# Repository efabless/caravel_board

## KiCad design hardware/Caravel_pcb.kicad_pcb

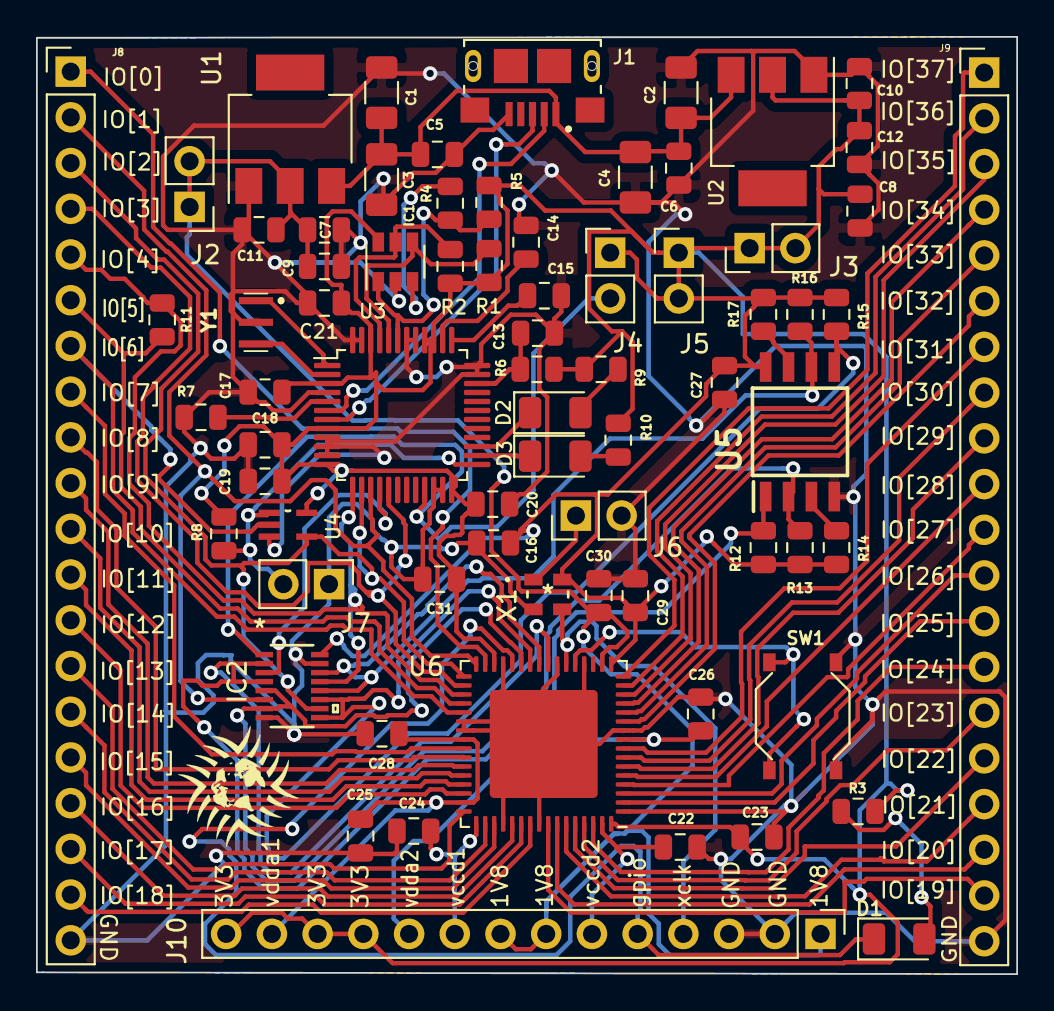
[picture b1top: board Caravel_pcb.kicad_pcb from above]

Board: 2 copper layers, 54.5 x 52.1 mm, 73 parts (0 on the bottom side), 76 nets.

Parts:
C1, C2, C3, C4: 100uf - GRM31CR60J107ME39L; C_1206_3216Metric
C5, C6, C9, C10: 10uf - CC0805KKX5R8BB106; C_0805_2012Metric
C7, C8: 22uf - CC0805MKX5R5BB226; C_0805_2012Metric
C11, C12: 1uf; C_0805_2012Metric
C13: 0.01uf - CC0805JRX7R9BB103; C_0805_2012Metric
C14, C15, C16, C17, C18, C19, C20, C21, C22, C23, C24, C25, C26, C27, C28, C29, C30, C31: 0.1uf - CC0805KRX7R9BB104; C_0805_2012Metric
D1, D2, D3: LED - 17-215SURC/S530-A2/TR8; LED_1206_3216Metric
IC1: 93C56; SOT-23-6
IC2: TMUX1574DYYR
J1: USB_B_Micro - 10118193-0001LF; FCI_10118193-0001LF
J2, J3, J4, J5, J6: Conn_01x02_Male; PinHeader_1x02_P2.54mm_Vertical
J7: Conn_01x02_Female; PinHeader_1x02_P2.54mm_Vertical
J8, J9: Conn_01x20_Female; PinHeader_1x20_P2.54mm_Vertical
J10: Conn_01x14_Female; PinHeader_1x14_P2.54mm_Vertical
R1, R2, R5, R6, R12, R13, R14, R15, R16, R17: 10k - RC0805FR-0710KL; R_0805_2012Metric
R3: 82 - 0805W8F820JT5E; R_0805_2012Metric
R4: 2K - CR0805J80202G; R_0805_2012Metric
R7: 12K 1% - 0805W8F1202T5E; R_0805_2012Metric
R8: 10k; R_0805_2012Metric
R9, R10: 150 - 0805W8J0151T5E; R_0805_2012Metric
R11: 0; R_0805_2012Metric
SW1: SW_Push - SKQGADE010; SW4-SMD-5.2X5.2X1.5MM
T1: Logo; logo
U1: AZ1117CH-1.8TRG1; SOT-223
U2: AZ1117-3.3; SOT-223
U3: FT232H; LQFP-48_7x7mm_P0.5mm
U4: SN74LVC1G125DCKR; SOT65P210X110-5N
U5: W25Q32FVSS; SOIC127P790X216-8N
U6: Caravel; QFN-64-1EP_9x9mm_P0.5mm_EP6x6mm
X1: DSC6001_10MHZ; DSC6001JE1A-010.0000
Y1: CSTNE12M0GH5L000R0

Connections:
+1V8: C7.2, C9.2, C11.2, C30.2, J2.1, J2.2, J10.1, J10.7, J10.8, U1.2, U6.18
+5V: C1.2, C2.2, C3.2, C4.2, C5.2, C6.2, J1.1, U1.3, U2.3
Caravel_CSB: IC2.2, IC2.4, R12.1, U5.1, U6.24
Caravel_D0: IC2.9, IC2.11, R15.1, U5.5, U6.26
Caravel_D1: IC2.5, IC2.7, R13.1, U5.2, U6.27
Caravel_SCK: IC2.12, IC2.14, R16.1, U5.6, U6.25
EECLK: IC1.4, R1.1, U3.44
EECS: IC1.5, R2.1, U3.45
EEDATA: IC1.1, R4.2, R5.2, U3.43
FTDI_D+: J1.3, U3.7
FTDI_D-: J1.2, U3.6
GND: C1.1, C2.1, C3.1, C4.1, C5.1, C6.1, C7.1, C8.1, C9.1, C10.1, C11.1, C12.1, C13.1, C14.1, C15.1, C16.1, C17.1, C18.1, C19.1, C20.1, C21.1, C22.1, C23.1, C24.2, C25.1, C26.1, C27.2, C28.2, C29.1, C30.1, C31.2, IC1.2, IC2.8, IC2.15, J1.5, J6.2, J7.1, J8.20, J9.20, J10.2, J10.3, R7.1, SW1.2, U1.1, U2.1, U3.4, U3.9, U3.10, U3.11, U3.22, U3.23, U3.35, U3.36, U3.41, U3.42, U3.47, U3.48, U4.3, U5.4, U6.1, U6.10, U6.20, U6.23, U6.29, U6.38, U6.39, U6.52, U6.56, U6.65, X1.2, Y1.2
unnamed: C13.2, R6.1, U3.34
unnamed: C14.2, U3.38
unnamed: C15.2, U3.37
unnamed: D1.2, R3.2
unnamed: D2.1, U3.27
unnamed: D2.2, R9.1
unnamed: D3.1, U3.26
unnamed: D3.2, R10.1
unnamed: IC1.3, R4.1
unnamed: J6.1, X1.1
unnamed: R7.2, U3.5
unnamed: R14.1, U5.3
unnamed: R17.1, U5.7
unnamed: U3.1, Y1.1
unnamed: U3.2, Y1.3
TMUX_SEL: IC2.1, J4.2, U3.21
TXD_EN: J7.2, R8.2, U3.25, U4.1
USB_CS1: IC2.3, U3.16
USB_CS2: J8.4, U3.17, U6.34
USB_SCK_TXD: IC2.13, J8.5, R11.2, U3.13, U6.35
USB_SI: IC2.6, J8.2, U3.15, U6.32
USB_SO_RXD: IC2.10, J8.3, U3.14, U4.4, U6.33
gpio: D1.1, J10.5, U6.28
mprj_io[0]: J8.1, U6.31
mprj_io[5]_ser_rx: J8.6, R11.1, U6.36
mprj_io[6]_ser_tx: J8.7, U4.2, U6.37
mprj_io[7]: J8.8, U6.41
mprj_io[8]: J8.9, U6.42
mprj_io[9]: J8.10, U6.43
mprj_io[10]: J8.11, U6.44
mprj_io[11]: J8.12, U6.45
mprj_io[12]: J8.13, U6.46
mprj_io[13]: J8.14, U6.48
mprj_io[14]: J8.15, U6.50
mprj_io[15]: J8.16, U6.51
mprj_io[16]: J8.17, U6.53
mprj_io[17]: J8.18, U6.54
mprj_io[18]: J8.19, U6.55
mprj_io[19]: J9.19, U6.57
mprj_io[20]: J9.18, U6.58
mprj_io[21]: J9.17, U6.59
mprj_io[22]: J9.16, U6.60
mprj_io[23]: J9.15, U6.61
mprj_io[24]: J9.14, U6.62
mprj_io[25]: J9.13, U6.2
mprj_io[26]: J9.12, U6.3
mprj_io[27]: J9.11, U6.4
mprj_io[28]: J9.10, U6.5
mprj_io[29]: J9.9, U6.6
mprj_io[30]: J9.8, U6.7
mprj_io[31]: J9.7, U6.8
mprj_io[32]: J9.6, U6.11
mprj_io[33]: J9.5, U6.12
mprj_io[34]: J9.4, U6.13
mprj_io[35]: J9.3, U6.14
mprj_io[36]: J9.2, U6.15
mprj_io[37]: J9.1, U6.16
vccd1: C24.1, J10.9, U6.49
vccd2: C22.2, J10.6, U6.63
vdda1: C25.2, C28.1, J10.13, U6.40, U6.47
vdda2: C26.2, J10.10, U6.9
vddio: C8.2, C10.2, C12.2, C16.2, C17.2, C18.2, C19.2, C20.2, C21.2, C23.2, C27.1, C29.2, C31.1, IC1.6, IC2.16, J3.1, J3.2, J4.1, J5.1, J5.2, J10.11, J10.12, J10.14, R1.2, R2.2, R3.1, R5.1, R6.2, R8.1, R9.2, R10.2, R12.2, R13.2, R14.2, R15.2, R16.2, R17.2, U2.2, U3.3, U3.8, U3.12, U3.24, U3.39, U3.40, U3.46, U4.5, U5.8, U6.17, U6.30, U6.64, X1.4
xclk: J10.4, U6.22, X1.3
~RST: SW1.1, U6.21

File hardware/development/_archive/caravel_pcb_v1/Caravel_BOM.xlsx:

Designators | QTY | Value | Part Number | Supplier
U6 | 1 |  | Caravel | EF
U5 | 1 |  | W25Q32JVSSIQ | DK
U4 | 1 |  | SN74LVC1G125DCKT | Mouser | alternative part
U3 | 1 |  | FT232H | not stocked
U2 | 1 |  | NCP1117LPST33T3G | DK | alternative part
U1 | 1 |  | AZ1117CH-1.8TRG1 | DK
IC1 | 0 |  | 93C56 | don't install
IC2 | 0 |  | TMUX1574DYYR | not stocked
D1, D2, D3 | 3 |  | LTST-C230KRKT | DK
C1, C2, C3, C4 | 4 | 100u | GMC31X5R107M6R3NT | DK | GMC31X5R107M6R3NT
C5, C6, C9, C10 | 4 | 10u | CC0805KKX5R8BB106 | DK
C7, C8 | 2 | 22u | CC0805MKX5R5BB226 | DK
C11, C12 | 2 | 1u | CC0805KKX7R8BB105 | DK
C14-C31 | 18 | 0.1u | CC0805KRX7R9BB104 | DK
C13 | 1 | 0.01u | CC0805JRX7R9BB103 | DK
R1, R2, R5, R6, R8, R12-R17 | 11 | 10K | RC0805FR-0710KL | DK
R7 | 1 | 12K, 1% | RMCF0805FT12K0 | DK
R9, R10 | 2 | 150 | RNCP0805FTD150R | DK
R3 | 1 | 82 | RMCF0805FT82R0 | DK
R4 | 1 | 2K | RMCF0805FT2K00 | DK
R11 | 1 | 0 | RK73Z2ATTD | DK
J1 | 1 |  | 10118193-0001LF | DK
X1 | 1 | 10MHz | DSC6001JE1A-010.0000 | DK
Y1 | 1 | 12MHz | CSTNE12M0GH5L000R0 | Mouser

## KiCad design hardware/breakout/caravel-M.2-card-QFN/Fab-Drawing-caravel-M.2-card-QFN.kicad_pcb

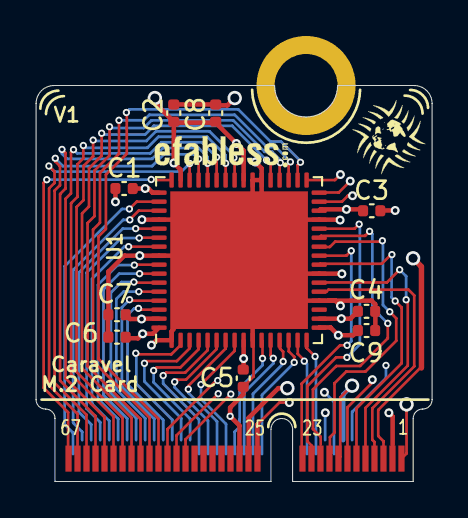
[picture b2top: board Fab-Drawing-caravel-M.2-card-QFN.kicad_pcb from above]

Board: 4 copper layers, 22.0 x 22.0 mm, 13 parts (0 on the bottom side), 53 nets.

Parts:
C1, C2, C3, C4, C5, C6, C7, C8, C9: 0.1uf; C_0402_1005Metric
J1: MICROMOD-2222-Generic; MicroMod-M.2-CARD-E-22
T1: Logo; logo_small
T2: Logo; ef_logo
U1: Caravel; QFN-64-1EP_9x9mm_P0.5mm_EP7.65x7.65mm

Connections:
Caravel_CSB: J1.11, U1.24 (flash_csb)
Caravel_D0: J1.17, U1.26 (flash_io0)
Caravel_D1: J1.19, U1.27 (flash_io1)
Caravel_SCK: J1.23, U1.25 (flash_clk)
GND: C1.1, C2.2, C3.2, C4.1, C5.1, C6.1, C7.1, C8.2, C9.1, J1.12, J1.18, J1.37 (P29), J1.GND, U1.1 (vssa2), U1.10 (vssd2), U1.20 (vssa), U1.23 (vssd), U1.29 (vssio), U1.38 (vssa1), U1.39 (vssd1), U1.52 (vssa1), U1.56 (vssio), U1.65 (ThermalPad)
gpio: J1.21, U1.28 (gpio)
mprj_io[0]: J1.49 (P41), U1.31 (mprj_io[0]_JTAG)
mprj_io[1]_SDO: J1.51 (P43), U1.32 (mprj_io[1]_SDO)
mprj_io[2]_SDI: J1.53 (P45), U1.33 (mprj_io[2]_SDI)
mprj_io[3]_CSB: J1.55 (P47), U1.34 (mprj_io[3]_CSB)
mprj_io[4]_SCK: J1.57 (P49), U1.35 (mprj_io[4]_SCK)
mprj_io[5]_ser_rx: J1.59 (P51), U1.36 (mprj_io[5]_ser_rx)
mprj_io[6]_ser_tx: J1.61 (P53), U1.37 (mprj_io[6]_ser_tx)
mprj_io[7]: J1.63 (P55), U1.41 (mprj_io[7])
mprj_io[8]: J1.65 (P57), U1.42 (mprj_io[8])
mprj_io[9]: J1.67 (P59), U1.43 (mprj_io[9])
mprj_io[10]: J1.69 (P61), U1.44 (mprj_io[10])
mprj_io[11]: J1.71 (P63), U1.45 (mprj_io[11])
mprj_io[12]: J1.73 (P65), U1.46 (mprj_io[12])
mprj_io[13]: J1.75 (P67), U1.48 (mprj_io[13])
mprj_io[14]: J1.74 (P66), U1.50 (mprj_io[14])
mprj_io[15]: J1.72 (P64), U1.51 (mprj_io[15])
mprj_io[16]: J1.70 (P62), U1.53 (mprj_io[16])
mprj_io[17]: J1.68 (P60), U1.54 (mprj_io[17])
mprj_io[18]: J1.66 (P58), U1.55 (mprj_io[18])
mprj_io[19]: J1.64 (P56), U1.57 (mprj_io[19])
mprj_io[20]: J1.62 (P54), U1.58 (mprj_io[20])
mprj_io[21]: J1.60 (P52), U1.59 (mprj_io[21])
mprj_io[22]: J1.58 (P50), U1.60 (mprj_io[22])
mprj_io[23]: J1.56 (P48), U1.61 (mprj_io[23])
mprj_io[24]: J1.54 (P46), U1.62 (mprj_io[24])
mprj_io[25]: J1.52 (P44), U1.2 (mprj_io[25])
mprj_io[26]: J1.50 (P42), U1.3 (mprj_io[26])
mprj_io[27]: J1.48 (P40), U1.4 (mprj_io[27])
mprj_io[28]: J1.46 (P38), U1.5 (mprj_io[28])
mprj_io[29]: J1.44 (P36), U1.6 (mprj_io[29])
mprj_io[30]: J1.42 (P34), U1.7 (mprj_io[30])
mprj_io[31]: J1.40 (P32), U1.8 (mprj_io[31])
mprj_io[32]: J1.38 (P30), U1.11 (mprj_io[32])
mprj_io[33]: J1.36 (P28), U1.12 (mprj_io[33])
mprj_io[34]: J1.34 (P26), U1.13 (mprj_io[34])
mprj_io[35]: J1.32 (P24), U1.14 (mprj_io[35])
mprj_io[36]: J1.22, U1.15 (mprj_io[36])
mprj_io[37]: J1.20, U1.16 (mprj_io[37])
vccd: C4.2, J1.14, J1.15, U1.18 (vccd)
vccd1: C1.2, J1.35 (P27), U1.49 (vccd1)
vccd2: C7.2, J1.1, U1.63 (vccd2)
vdda: C3.1, J1.5, U1.30 (vdda)
vdda1: C2.1, C8.1, J1.33 (P25), U1.40 (vdda1), U1.47 (vdda1)
vdda2: C5.2, J1.13, U1.9 (vdda2)
vddio: C6.2, C9.2, J1.3, J1.16, U1.17 (vddio), U1.64 (vddio)
xclk: J1.9, U1.22 (clock)
~RST: J1.7, U1.21 (resetb)

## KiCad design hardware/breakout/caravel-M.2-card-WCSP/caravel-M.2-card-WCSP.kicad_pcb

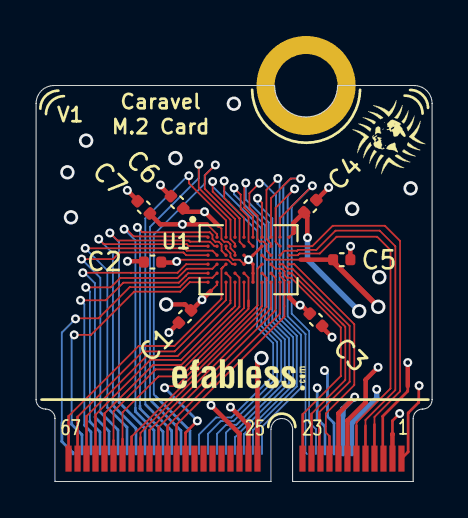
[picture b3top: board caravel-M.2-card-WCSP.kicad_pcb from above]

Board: 4 copper layers, 22.0 x 22.0 mm, 11 parts (0 on the bottom side), 53 nets.

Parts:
C1, C2, C3, C4, C5, C6, C7: 0.1uf; C_0402_1005Metric
J1: MICROMOD-2222-Generic; MicroMod-M.2-CARD-E-22
T1: Logo; logo_small
T2: Logo; ef_logo
U1: Caravel; Caravel_WCSP

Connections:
Caravel_CSB: J1.11, U1.C10 (flash_csb)
Caravel_D0: J1.17, U1.D10 (flash_io0)
Caravel_D1: J1.19, U1.D9 (flash_io1)
Caravel_SCK: J1.23, U1.D8 (flash_clk)
GND: C1.1, C2.2, C3.2, C4.1, C5.1, C6.1, C7.1, J1.12, J1.18, J1.37 (P29), J1.GND, U1.B3 (vssa2), U1.B7 (vssd2), U1.C5 (vssa/vssd/vssio), U1.C6 (vssa/vssd/vssio), U1.D5 (vssa/vssd/vssio), U1.D6 (vssa/vssd/vssio), U1.E6 (vssa1), U1.F6 (vssd1)
gpio: J1.21, U1.E10 (gpio)
mprj_io[0]: J1.49 (P41), U1.D7 (mprj_io[0]_JTAG)
mprj_io[1]_SDO: J1.51 (P43), U1.E9 (mprj_io[1]_SDO)
mprj_io[2]_SDI: J1.53 (P45), U1.F9 (mprj_io[2]_SDI)
mprj_io[3]_CSB: J1.55 (P47), U1.E8 (mprj_io[3]_CSB)
mprj_io[4]_SCK: J1.57 (P49), U1.F8 (mprj_io[4]_SCK)
mprj_io[5]_ser_rx: J1.59 (P51), U1.E7 (mprj_io[5]_ser_rx)
mprj_io[6]_ser_tx: J1.61 (P53), U1.F7 (mprj_io[6]_ser_tx)
mprj_io[7]: J1.63 (P55), U1.E5 (mprj_io[7]_IRQ)
mprj_io[8]: J1.65 (P57), U1.F5 (mprj_io[8]_flash_csb)
mprj_io[9]: J1.67 (P59), U1.E4 (mprj_io[9]_flash2_sck)
mprj_io[10]: J1.69 (P61), U1.F4 (mprj_io[10]_flash_io0)
mprj_io[11]: J1.71 (P63), U1.E3 (mprj_io[11]_flash2_io1)
mprj_io[12]: J1.73 (P65), U1.F3 (mprj_io[12])
mprj_io[13]: J1.75 (P67), U1.D3 (mprj_io[13])
mprj_io[14]: J1.74 (P66), U1.E2 (mprj_io[14])
mprj_io[15]: J1.72 (P64), U1.F1 (mprj_io[15])
mprj_io[16]: J1.70 (P62), U1.E1 (mprj_io[16])
mprj_io[17]: J1.68 (P60), U1.D2 (mprj_io[17])
mprj_io[18]: J1.66 (P58), U1.D1 (mprj_io[18])
mprj_io[19]: J1.64 (P56), U1.C1 (mprj_io[19])
mprj_io[20]: J1.62 (P54), U1.C2 (mprj_io[20])
mprj_io[21]: J1.60 (P52), U1.B1 (mprj_io[21])
mprj_io[22]: J1.58 (P50), U1.B2 (mprj_io[22])
mprj_io[23]: J1.56 (P48), U1.A1 (mprj_io[23])
mprj_io[24]: J1.54 (P46), U1.C3 (mprj_io[24])
mprj_io[25]: J1.52 (P44), U1.A3 (mprj_io[25])
mprj_io[26]: J1.50 (P42), U1.B4 (mprj_io[26])
mprj_io[27]: J1.48 (P40), U1.A4 (mprj_io[27])
mprj_io[28]: J1.46 (P38), U1.B5 (mprj_io[28])
mprj_io[29]: J1.44 (P36), U1.A5 (mprj_io[29])
mprj_io[30]: J1.42 (P34), U1.B6 (mprj_io[30])
mprj_io[31]: J1.40 (P32), U1.A6 (mprj_io[31])
mprj_io[32]: J1.38 (P30), U1.A7 (mprj_io[32])
mprj_io[33]: J1.36 (P28), U1.C8 (mprj_io[33])
mprj_io[34]: J1.34 (P26), U1.B8 (mprj_io[34])
mprj_io[35]: J1.32 (P24), U1.A8 (mprj_io[35])
mprj_io[36]: J1.22, U1.B9 (mprj_io[36])
mprj_io[37]: J1.20, U1.A9 (mprj_io[37])
vccd: C4.2, J1.14, J1.15, U1.A10 (vccd)
vccd1: C1.2, J1.35 (P27), U1.F2 (vccd1)
vccd2: C7.2, J1.1, U1.A2 (vccd2)
vdda: C3.1, J1.5, U1.F10 (vdda)
vdda1: C2.1, J1.33 (P25), U1.D4 (vdda1)
vdda2: C5.2, J1.13, U1.C7 (vdda2)
vddio: C6.2, J1.3, J1.16, U1.C4 (vddio)
xclk: J1.9, U1.C9 (clock)
~RST: J1.7, U1.B10 (resetb)

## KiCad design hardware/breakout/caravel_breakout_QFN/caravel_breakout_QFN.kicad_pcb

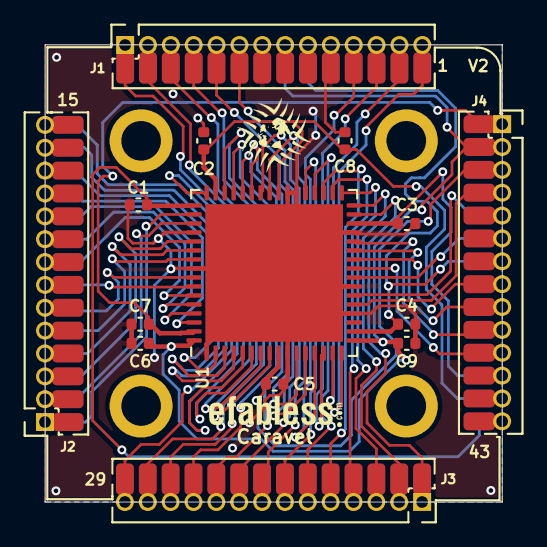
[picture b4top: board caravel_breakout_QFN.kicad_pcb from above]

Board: 2 copper layers, 25.4 x 25.4 mm, 20 parts (0 on the bottom side), 53 nets.

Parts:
C1, C2, C3, C4, C5, C6, C7, C8, C9: 0.1uf; C_0402_1005Metric
H1, H2, H3, H4: Positioning Holes; MountingHole_2.2mm_M2_ISO7380_Pad
J1, J2, J3, J4: Conn_01x14_Female; Caravel_Breakout_Connectors_2x14
T1: Logo; logo_small
T2: Logo; ef_logo
U1: Caravel; QFN-64-1EP_9x9mm_P0.5mm_EP7.65x7.65mm

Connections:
Caravel_CSB: J4.6, U1.24 (flash_csb)
Caravel_D0: J4.8, U1.26 (flash_io0)
Caravel_D1: J4.9, U1.27 (flash_io1)
Caravel_SCK: J4.11, U1.25 (flash_clk)
GND: C1.1, C2.2, C3.2, C4.1, C5.1, C6.1, C7.1, C8.2, C9.1, J1.7, J1.10, U1.1 (vssa2), U1.10 (vssd2), U1.20 (vssa), U1.23 (vssd), U1.29 (vssio), U1.38 (vssa1), U1.39 (vssd1), U1.52 (vssa1), U1.56 (vssio), U1.65 (ThermalPad)
gpio: J4.10, U1.28 (gpio)
mprj_io[0]: J3.1, U1.31 (mprj_io[0]_JTAG)
mprj_io[1]_SDO: J3.2, U1.32 (mprj_io[1]_SDO)
mprj_io[2]_SDI: J3.3, U1.33 (mprj_io[2]_SDI)
mprj_io[3]_CSB: J3.4, U1.34 (mprj_io[3]_CSB)
mprj_io[4]_SCK: J3.5, U1.35 (mprj_io[4]_SCK)
mprj_io[5]_ser_rx: J3.6, U1.36 (mprj_io[5]_ser_rx)
mprj_io[6]_ser_tx: J3.7, U1.37 (mprj_io[6]_ser_tx)
mprj_io[7]: J3.8, U1.41 (mprj_io[7])
mprj_io[8]: J3.9, U1.42 (mprj_io[8])
mprj_io[9]: J3.10, U1.43 (mprj_io[9])
mprj_io[10]: J3.11, U1.44 (mprj_io[10])
mprj_io[11]: J3.12, U1.45 (mprj_io[11])
mprj_io[12]: J3.13, U1.46 (mprj_io[12])
mprj_io[13]: J3.14, U1.48 (mprj_io[13])
mprj_io[14]: J2.1, U1.50 (mprj_io[14])
mprj_io[15]: J2.2, U1.51 (mprj_io[15])
mprj_io[16]: J2.3, U1.53 (mprj_io[16])
mprj_io[17]: J2.4, U1.54 (mprj_io[17])
mprj_io[18]: J2.5, U1.55 (mprj_io[18])
mprj_io[19]: J2.6, U1.57 (mprj_io[19])
mprj_io[20]: J2.7, U1.58 (mprj_io[20])
mprj_io[21]: J2.8, U1.59 (mprj_io[21])
mprj_io[22]: J2.9, U1.60 (mprj_io[22])
mprj_io[23]: J2.10, U1.61 (mprj_io[23])
mprj_io[24]: J2.11, U1.62 (mprj_io[24])
mprj_io[25]: J2.12, U1.2 (mprj_io[25])
mprj_io[26]: J2.13, U1.3 (mprj_io[26])
mprj_io[27]: J2.14, U1.4 (mprj_io[27])
mprj_io[28]: J1.1, U1.5 (mprj_io[28])
mprj_io[29]: J1.2, U1.6 (mprj_io[29])
mprj_io[30]: J1.3, U1.7 (mprj_io[30])
mprj_io[31]: J1.4, U1.8 (mprj_io[31])
mprj_io[32]: J1.5, U1.11 (mprj_io[32])
mprj_io[33]: J1.6, U1.12 (mprj_io[33])
mprj_io[34]: J1.11, U1.13 (mprj_io[34])
mprj_io[35]: J1.12, U1.14 (mprj_io[35])
mprj_io[36]: J1.13, U1.15 (mprj_io[36])
mprj_io[37]: J1.14, U1.16 (mprj_io[37])
vccd: C4.2, J1.9, J4.7, U1.18 (vccd)
vccd1: C1.2, J4.14, U1.49 (vccd1)
vccd2: C7.2, J4.1, U1.63 (vccd2)
vdda: C3.1, J4.12, U1.30 (vdda)
vdda1: C2.1, C8.1, J4.13, U1.40 (vdda1), U1.47 (vdda1)
vdda2: C5.2, J4.3, U1.9 (vdda2)
vddio: C6.2, C9.2, J1.8, J4.2, U1.17 (vddio), U1.64 (vddio)
xclk: J4.5, U1.22 (clock)
~RST: J4.4, U1.21 (resetb)

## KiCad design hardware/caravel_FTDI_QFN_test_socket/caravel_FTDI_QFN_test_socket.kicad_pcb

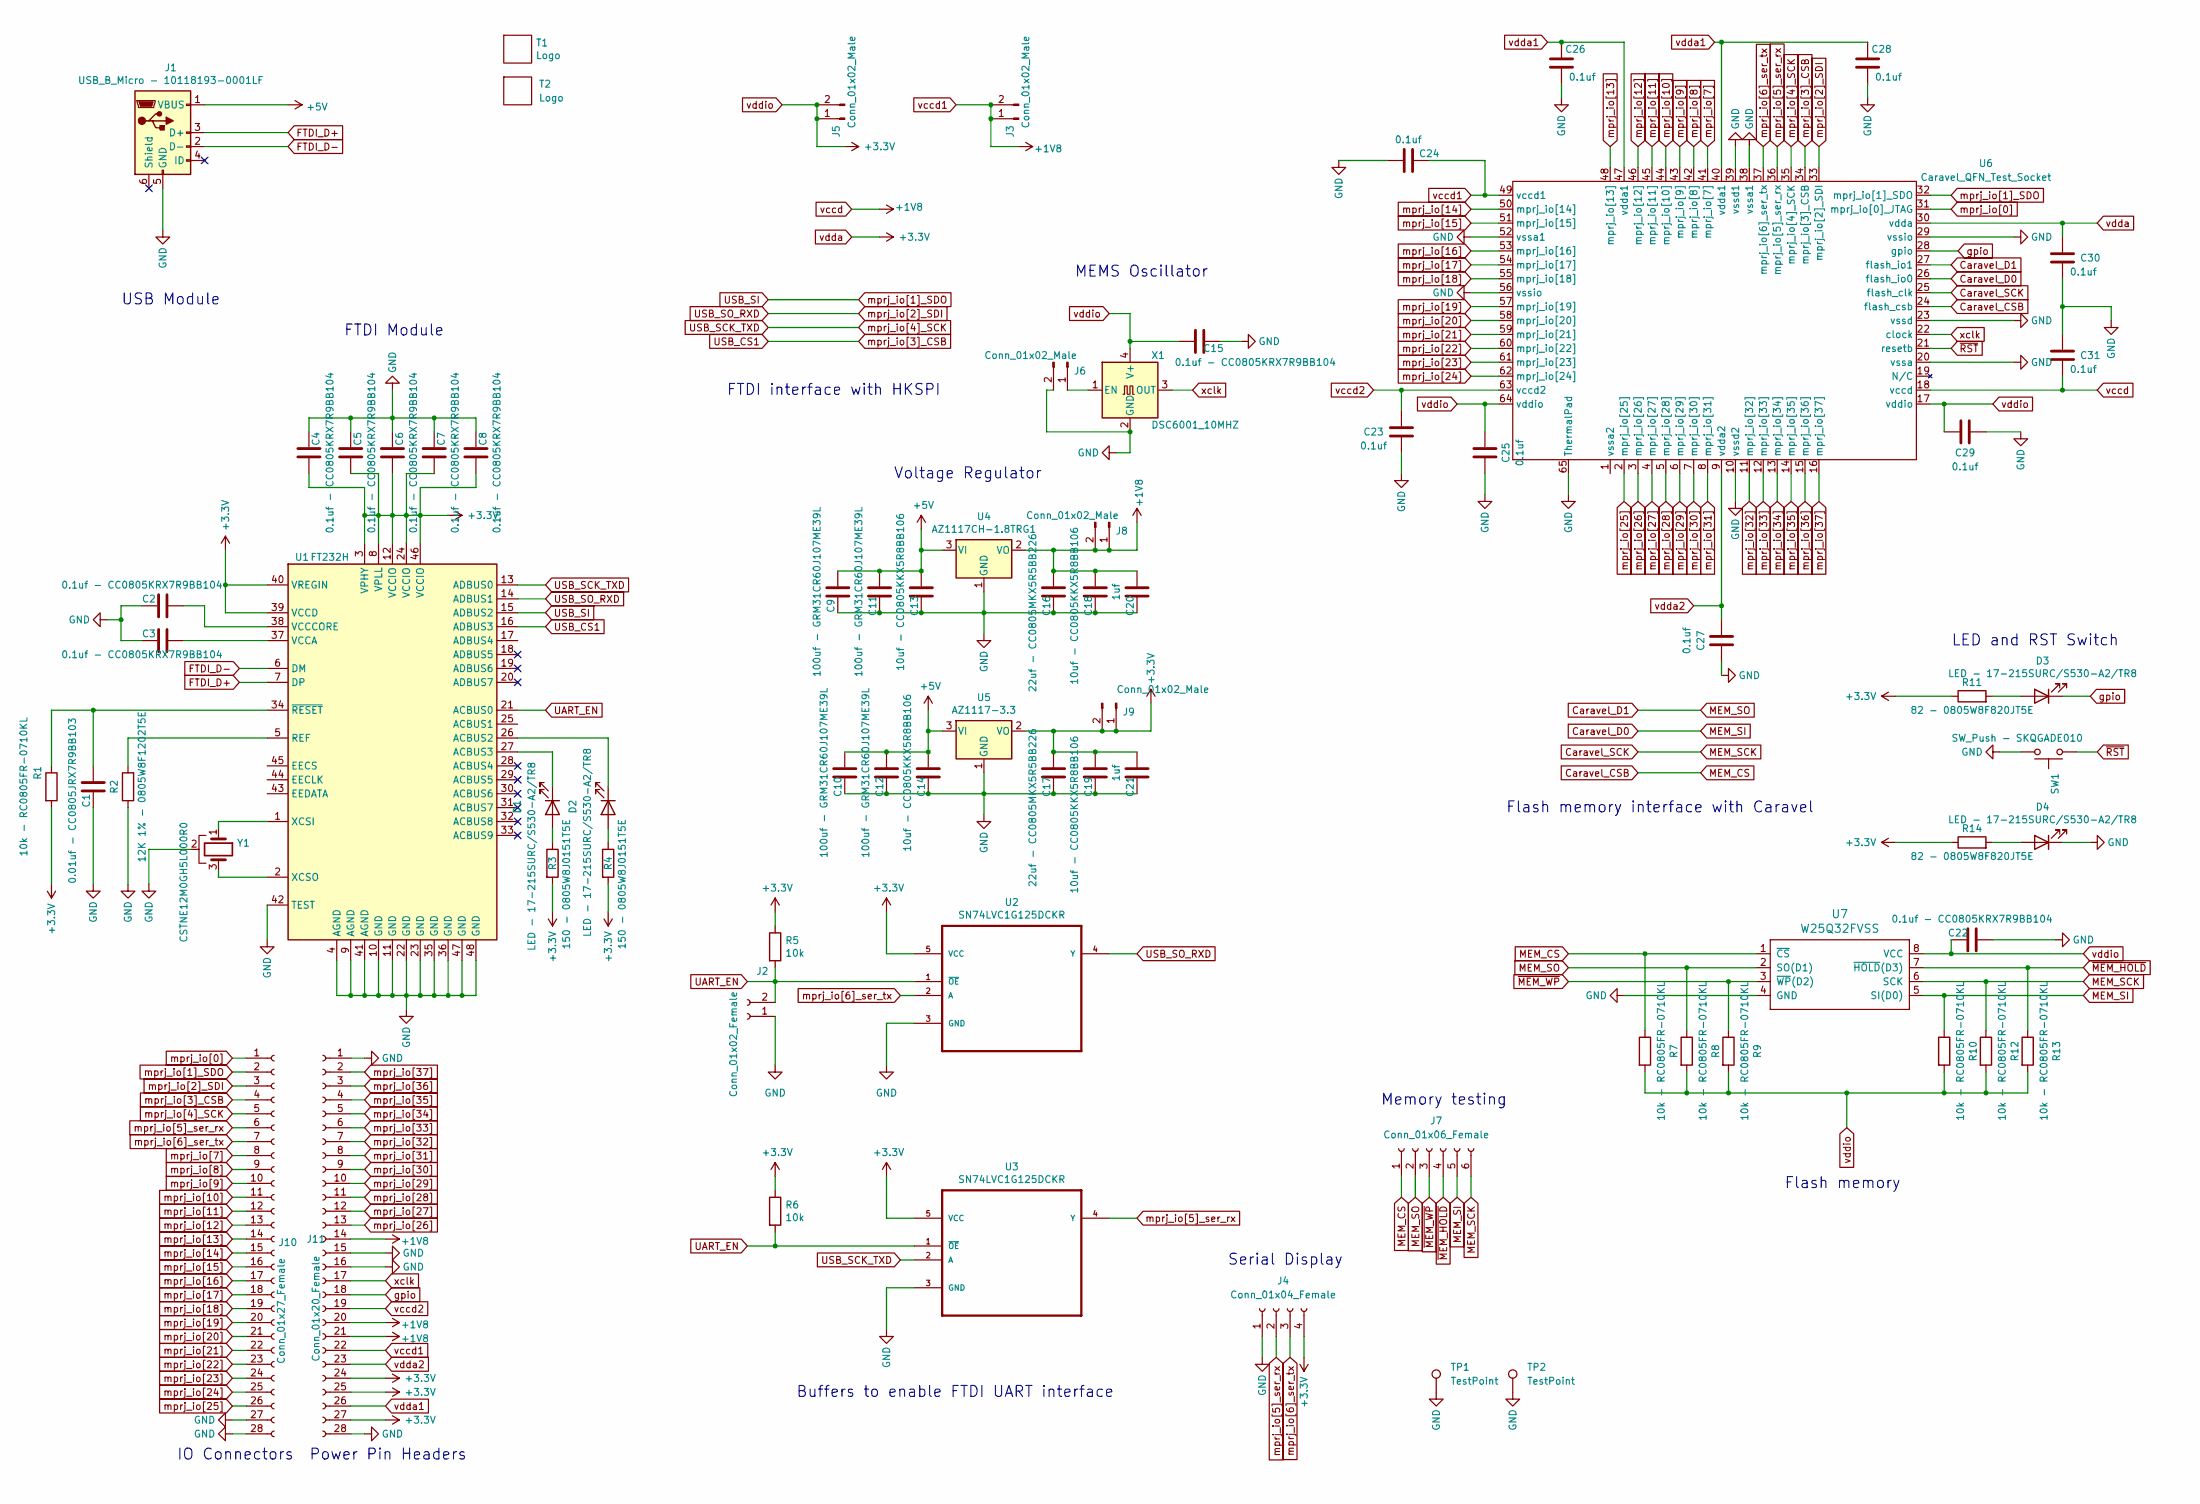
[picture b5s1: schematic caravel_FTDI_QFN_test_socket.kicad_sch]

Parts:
C1: 0.01uf - CC0805JRX7R9BB103; C_0805_2012Metric
C2, C3, C4, C5, C6, C7, C8, C15, C22: 0.1uf - CC0805KRX7R9BB104; C_0805_2012Metric
C9, C10, C11, C12: 100uf - GRM31CR60J107ME39L; C_1206_3216Metric
C13, C14, C18, C19: 10uf - CC0805KKX5R8BB106; C_0805_2012Metric
C16, C17: 22uf - CC0805MKX5R5BB226; C_0805_2012Metric
C20, C21: 1uf; C_0805_2012Metric
C23, C24, C25, C26, C27, C28, C29, C30, C31: 0.1uf; C_0805_2012Metric
D1, D2, D3, D4: LED - 17-215SURC/S530-A2/TR8; LED_1206_3216Metric
J1: USB_B_Micro - 10118193-0001LF; FCI_10118193-0001LF
J2: Conn_01x02_Female; PinHeader_1x02_P2.54mm_Vertical
J3, J5, J6, J8, J9: Conn_01x02_Male; PinHeader_1x02_P2.54mm_Vertical
J4: Conn_01x04_Female; PinHeader_1x04_P2.54mm_Vertical
J7: Conn_01x06_Female; PinHeader_1x06_P2.54mm_Vertical
J10: Conn_01x27_Female; PinHeader_1x27_P2.54mm_Vertical
J11: Conn_01x20_Female; PinHeader_1x20_P2.54mm_Vertical
R1, R7, R8, R9, R10, R12, R13: 10k - RC0805FR-0710KL; R_0805_2012Metric
R2: 12K 1% - 0805W8F1202T5E; R_0805_2012Metric
R3, R4: 150 - 0805W8J0151T5E; R_0805_2012Metric
R5, R6: 10k; R_0805_2012Metric
R11, R14: 82 - 0805W8F820JT5E; R_0805_2012Metric
SW1: SW_Push - SKQGADE010; SW4-SMD-5.2X5.2X1.5MM
T1: Logo; logo
T2: Logo; ef_logo
TP1, TP2: TestPoint; TestPoint_Bridge_Pitch2.54mm_Drill1.0mm
U1: FT232H; QFN-48-1EP_8x8mm_P0.5mm_EP6.2x6.2mm
U2, U3: SN74LVC1G125DCKR; SOT65P210X110-5N
U4: AZ1117CH-1.8TRG1; SOT-223
U5: AZ1117-3.3; SOT-223
U6: Caravel_QFN_Test_Socket; QFN64_(9x9)_0.5_CL_Test_Socket
U7: W25Q32FVSS; SOIC127P790X216-8N
X1: DSC6001_10MHZ; DSC6001JE1A-010.0000
Y1: CSTNE12M0GH5L000R0

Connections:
+5V: C9.2, C10.2, C11.2, C12.2, C13.2, C14.2, J1.1 (VBUS), U4.3 (VI), U5.3 (VI)
Caravel_CSB: J7.1, R7.1, U6.24 (flash_csb), U7.1 (~CS)
Caravel_D0: J7.5, R10.1, U6.26 (flash_io0), U7.5 (SI(D0))
Caravel_D1: J7.2, R8.1, U6.27 (flash_io1), U7.2 (SO(D1))
Caravel_SCK: J7.6, R12.1, U6.25 (flash_clk), U7.6 (SCK)
FTDI_D+: J1.3 (D+), U1.7 (DP)
FTDI_D-: J1.2 (D-), U1.6 (DM)
GND: C1.1, C2.1, C3.1, C4.1, C5.1, C6.1, C7.1, C8.1, C9.1, C10.1, C11.1, C12.1, C13.1, C14.1, C15.1, C16.1, C17.1, C18.1, C19.1, C20.1, C21.1, C22.2, C23.1, C24.1, C25.1, C26.2, C27.1, C28.2, C29.1, C30.2, C31.1, D4.1 (K), J1.5 (GND), J2.1, J4.1, J6.2, J10.27, J10.28, J11.1, J11.15, J11.16, J11.28, R2.1, SW1.2, TP1.1, TP2.1, U1.4 (AGND), U1.9 (AGND), U1.10 (GND), U1.11 (GND), U1.22 (GND), U1.23 (GND), U1.35 (GND), U1.36 (GND), U1.41 (AGND), U1.42 (TEST), U1.47 (GND), U1.48 (GND), U2.3 (GND), U3.3 (GND), U4.1 (GND), U5.1 (GND), U6.10 (vssd2), U6.20 (vssa), U6.23 (vssd), U6.29 (vssio), U6.38 (vssa1), U6.39 (vssd1), U6.52 (vssa1), U6.56 (vssio), U6.65 (ThermalPad), U7.4 (GND), X1.2 (GND), Y1.2
unnamed: C1.2, R1.1, U1.34 (~RESET)
unnamed: C2.2, U1.38 (VCCCORE)
unnamed: C3.2, U1.37 (VCCA)
unnamed: D1.1 (K), U1.27 (ACBUS3)
unnamed: D1.2 (A), R3.1
unnamed: D2.1 (K), U1.26 (ACBUS2)
unnamed: D2.2 (A), R4.1
unnamed: D3.2 (A), R11.2
unnamed: D4.2 (A), R14.2
unnamed: J6.1, X1.1 (EN)
unnamed: R2.2, U1.5 (REF)
unnamed: U1.1 (XCSI), Y1.1
unnamed: U1.2 (XCSO), Y1.3
UART_EN: J2.2, R5.2, R6.2, U1.21 (ACBUS0), U2.1 (~OE), U3.1 (~OE)
USB_CS1: J10.4, U1.16 (ADBUS3), U6.34 (mprj_io[3]_CSB)
USB_SCK_TXD: J10.5, U1.13 (ADBUS0), U3.2 (A), U6.35 (mprj_io[4]_SCK)
USB_SI: J10.2, U1.15 (ADBUS2), U6.32 (mprj_io[1]_SDO)
USB_SO_RXD: J10.3, U1.14 (ADBUS1), U2.4 (Y), U6.33 (mprj_io[2]_SDI)
gpio: D3.1 (K), J11.18, U6.28 (gpio)
mprj_io[0]: J10.1, U6.31 (mprj_io[0]_JTAG)
mprj_io[5]_ser_rx: J4.2, J10.6, U3.4 (Y), U6.36 (mprj_io[5]_ser_rx)
mprj_io[6]_ser_tx: J4.3, J10.7, U2.2 (A), U6.37 (mprj_io[6]_ser_tx)
mprj_io[7]: J10.8, U6.41 (mprj_io[7])
mprj_io[8]: J10.9, U6.42 (mprj_io[8])
mprj_io[9]: J10.10, U6.43 (mprj_io[9])
mprj_io[10]: J10.11, U6.44 (mprj_io[10])
mprj_io[11]: J10.12, U6.45 (mprj_io[11])
mprj_io[12]: J10.13, U6.46 (mprj_io[12])
mprj_io[13]: J10.14, U6.48 (mprj_io[13])
mprj_io[14]: J10.15, U6.50 (mprj_io[14])
mprj_io[15]: J10.16, U6.51 (mprj_io[15])
mprj_io[16]: J10.17, U6.53 (mprj_io[16])
mprj_io[17]: J10.18, U6.54 (mprj_io[17])
mprj_io[18]: J10.19, U6.55 (mprj_io[18])
mprj_io[19]: J10.20, U6.57 (mprj_io[19])
mprj_io[20]: J10.21, U6.58 (mprj_io[20])
mprj_io[21]: J10.22, U6.59 (mprj_io[21])
mprj_io[22]: J10.23, U6.60 (mprj_io[22])
mprj_io[23]: J10.24, U6.61 (mprj_io[23])
mprj_io[24]: J10.25, U6.62 (mprj_io[24])
mprj_io[25]: J10.26, U6.2 (mprj_io[25])
mprj_io[26]: J11.13, U6.3 (mprj_io[26])
mprj_io[27]: J11.12, U6.4 (mprj_io[27])
mprj_io[28]: J11.11, U6.5 (mprj_io[28])
mprj_io[29]: J11.10, U6.6 (mprj_io[29])
mprj_io[30]: J11.9, U6.7 (mprj_io[30])
mprj_io[31]: J11.8, U6.8 (mprj_io[31])
mprj_io[32]: J11.7, U6.11 (mprj_io[32])
mprj_io[33]: J11.6, U6.12 (mprj_io[33])
mprj_io[34]: J11.5, U6.13 (mprj_io[34])
mprj_io[35]: J11.4, U6.14 (mprj_io[35])
mprj_io[36]: J11.3, U6.15 (mprj_io[36])
mprj_io[37]: J11.2, U6.16 (mprj_io[37])
vccd: C16.2, C18.2, C20.2, C24.2, C31.2, J3.1, J3.2, J8.1, J8.2, J11.14, J11.20, J11.21, J11.22, U4.2 (VO), U6.18 (vccd), U6.49 (vccd1)
vccd2: C23.2, J11.19, U6.63 (vccd2)
vdda: C4.2, C5.2, C6.2, C7.2, C8.2, C15.2, C17.2, C19.2, C21.2, C22.1, C25.2, C29.2, C30.1, J4.4, J5.1, J5.2, J9.1, J9.2, J11.24, J11.25, J11.27, R1.2, R3.2, R4.2, R5.1, R6.1, R7.2, R8.2, R9.2, R10.2, R11.1, R12.2, R13.2, R14.1, U1.3 (VPHY), U1.8 (VPLL), U1.12 (VCCIO), U1.24 (VCCIO), U1.39 (VCCD), U1.40 (VREGIN), U1.46 (VCCIO), U2.5 (VCC), U3.5 (VCC), U5.2 (VO), U6.17 (vddio), U6.30 (vdda), U6.64 (vddio), U7.8 (VCC), X1.4 (V+)
vdda1: C26.1, C28.1, J11.26, U6.40 (vdda1), U6.47 (vdda1)
vdda2: C27.2, J11.23, U6.9 (vdda2)
xclk: J11.17, U6.22 (clock), X1.3 (OUT)
~MEM_HOLD: J7.4, R13.1, U7.7 (~HOLD(D3))
~MEM_WP: J7.3, R9.1, U7.3 (~WP(D2))
~RST: SW1.1, U6.21 (resetb)

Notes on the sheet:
Serial Display
LED and RST Switch
Flash memory interface with Caravel
Flash memory
Memory testing
FTDI interface with HKSPI
Power Pin Headers
Voltage Regulator
IO Connectors
FTDI Module
USB Module
MEMS Oscillator
Buffers to enable FTDI UART interface

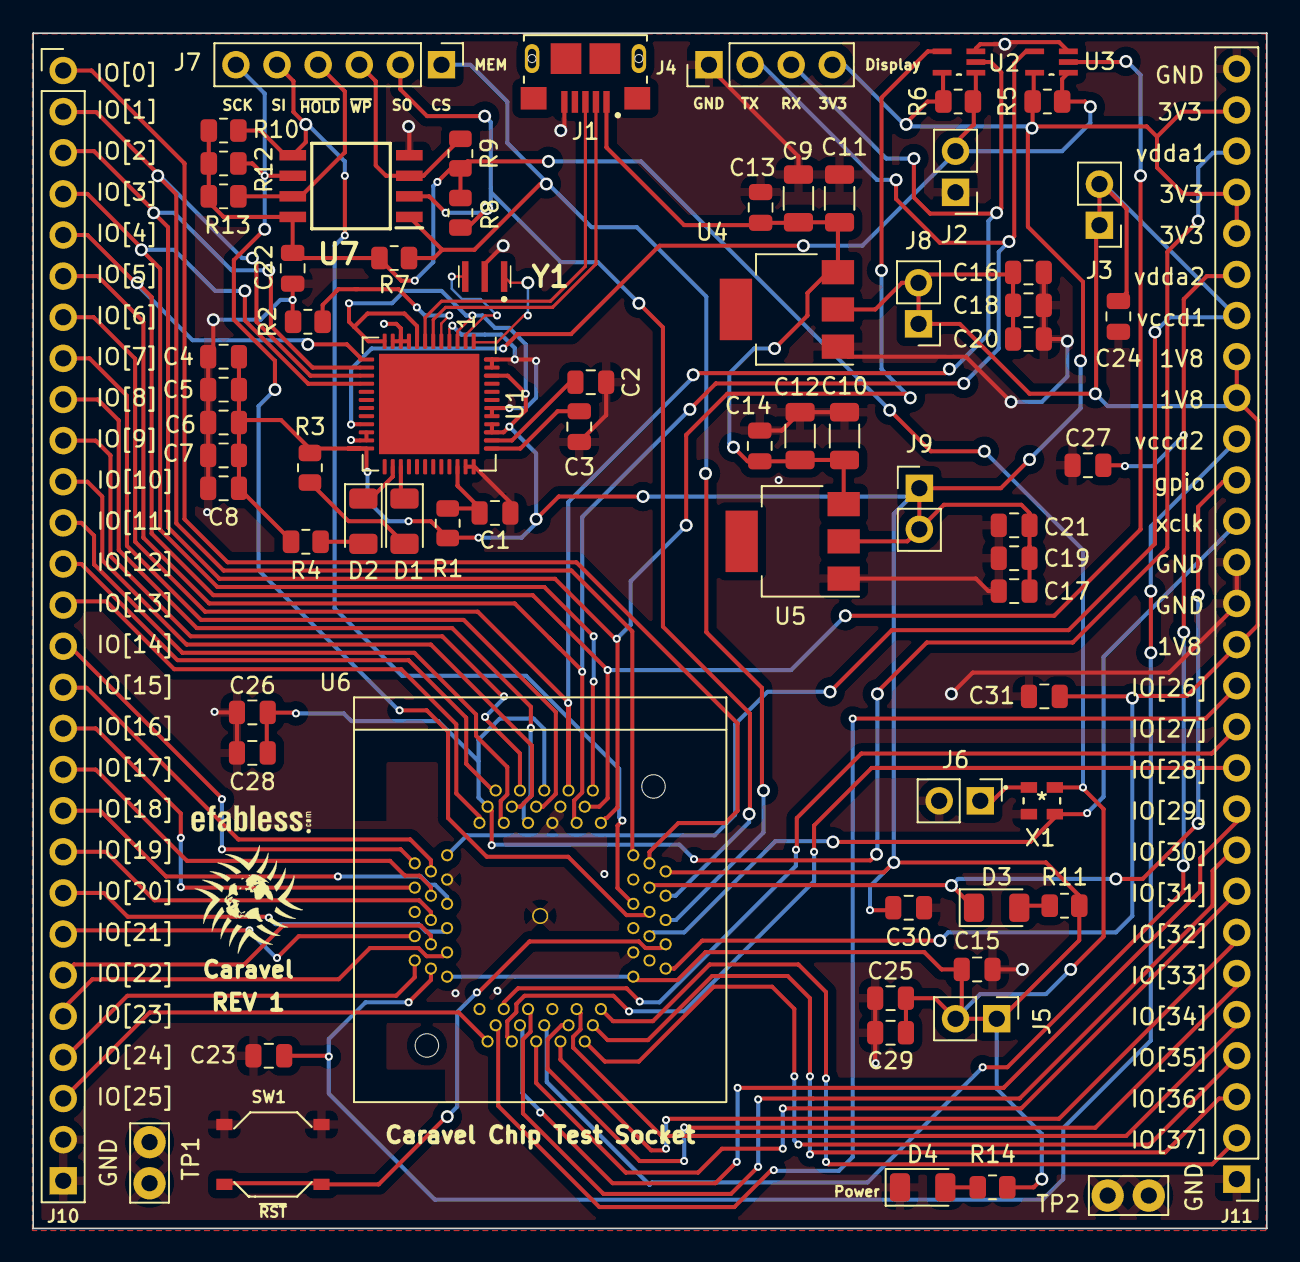
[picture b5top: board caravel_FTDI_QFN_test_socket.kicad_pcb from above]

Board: 2 copper layers, 76.2 x 73.8 mm, 74 parts (0 on the bottom side), 70 nets.

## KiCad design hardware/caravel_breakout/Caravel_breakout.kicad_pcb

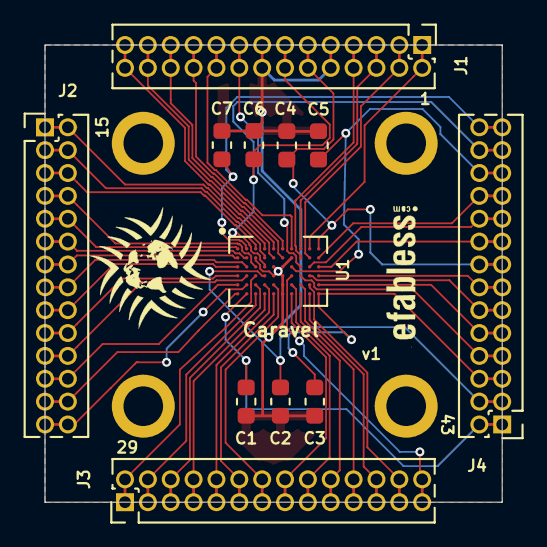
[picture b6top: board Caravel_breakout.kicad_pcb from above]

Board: 2 copper layers, 25.4 x 25.4 mm, 18 parts (0 on the bottom side), 53 nets.

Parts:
C1, C2, C3, C4, C5, C6, C7: 0.1uf; C_0603_1608Metric
H1, H2, H3, H4: Positioning Holes; MountingHole_2.2mm_M2_ISO7380_Pad
J1, J2, J3, J4: Conn_01x14_Female; PinHeader_2x14_P1.27mm_Vertical
T1: Logo; logo
T2: Logo; ef_logo
U1: Caravel; Caravel_WCSP

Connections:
Caravel_CSB: J4.17, J4.18, U1.C10
Caravel_D0: J4.13, J4.14, U1.D10
Caravel_D1: J4.11, J4.12, U1.D9
Caravel_SCK: J4.7, J4.8, U1.D8
GND: C1.1, C2.2, C3.2, C4.1, C5.1, C6.1, C7.1, J1.9, J1.10, J1.15, J1.16, U1.B3, U1.B7, U1.C5, U1.C6, U1.D5, U1.D6, U1.E6, U1.F6
gpio: J4.9, J4.10, U1.E10
mprj_io[0]: J3.27, J3.28, U1.D7
mprj_io[1]_SDO: J3.25, J3.26, U1.E9
mprj_io[2]_SDI: J3.23, J3.24, U1.F9
mprj_io[3]_CSB: J3.21, J3.22, U1.E8
mprj_io[4]_SCK: J3.19, J3.20, U1.F8
mprj_io[5]_ser_rx: J3.17, J3.18, U1.E7
mprj_io[6]_ser_tx: J3.15, J3.16, U1.F7
mprj_io[7]: J3.13, J3.14, U1.E5
mprj_io[8]: J3.11, J3.12, U1.F5
mprj_io[9]: J3.9, J3.10, U1.E4
mprj_io[10]: J3.7, J3.8, U1.F4
mprj_io[11]: J3.5, J3.6, U1.E3
mprj_io[12]: J3.3, J3.4, U1.F3
mprj_io[13]: J3.1, J3.2, U1.D3
mprj_io[14]: J2.27, J2.28, U1.E2
mprj_io[15]: J2.25, J2.26, U1.F1
mprj_io[16]: J2.23, J2.24, U1.E1
mprj_io[17]: J2.21, J2.22, U1.D2
mprj_io[18]: J2.19, J2.20, U1.D1
mprj_io[19]: J2.17, J2.18, U1.C1
mprj_io[20]: J2.15, J2.16, U1.C2
mprj_io[21]: J2.13, J2.14, U1.B1
mprj_io[22]: J2.11, J2.12, U1.B2
mprj_io[23]: J2.9, J2.10, U1.A1
mprj_io[24]: J2.7, J2.8, U1.C3
mprj_io[25]: J2.5, J2.6, U1.A3
mprj_io[26]: J2.3, J2.4, U1.B4
mprj_io[27]: J2.1, J2.2, U1.A4
mprj_io[28]: J1.27, J1.28, U1.B5
mprj_io[29]: J1.25, J1.26, U1.A5
mprj_io[30]: J1.23, J1.24, U1.B6
mprj_io[31]: J1.21, J1.22, U1.A6
mprj_io[32]: J1.19, J1.20, U1.A7
mprj_io[33]: J1.17, J1.18, U1.C8
mprj_io[34]: J1.7, J1.8, U1.B8
mprj_io[35]: J1.5, J1.6, U1.A8
mprj_io[36]: J1.3, J1.4, U1.B9
mprj_io[37]: J1.1, J1.2, U1.A9
vccd: C4.2, J1.11, J1.12, J4.15, J4.16, U1.A10
vccd1: C1.2, J4.1, J4.2, U1.F2
vccd2: C7.2, J4.27, J4.28, U1.A2
vdda: C3.1, J4.5, J4.6, U1.F10
vdda1: C2.1, J4.3, J4.4, U1.D4
vdda2: C5.2, J4.23, J4.24, U1.C7
vddio: C6.2, J1.13, J1.14, J4.25, J4.26, U1.C4
xclk: J4.19, J4.20, U1.C9
~RST: J4.21, J4.22, U1.B10

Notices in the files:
parts and their libraries:
Copyright 2016 Accelerated Designs. All rights reserved.
